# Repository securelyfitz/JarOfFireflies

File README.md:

# Jar of Fireflies
ATtiny-based Jar of Fireflies soldering project with inspiration and reuse from jason webb's https://github.com/jasonwebb/Jar-of-Fireflies

## Hardware Description
This project is intended to be a simple soldering project based on the ATTiny using only a handful of through-hole components. It uses 3 I/O pins to drive 6 charlieplexed LEDs, and an additional 2 I/O pins to control a capacitive sensor.

I originally intended to have the jar's metal ring be touch sensitive alone. However, for cap sensing to work, you need to be grounded, and a PCB inside a glass jar isn't exactly grounded. To account for that, there are several exposed ground pads just inside the ring - touch the ring and one of those pads, and the cap sensing should work.

## Bill of Materials:
* 3x 150 Ohm Resistor
* 2x 1K Ohm Resistor
* 1x 1M Ohm Resistor
* 1x ATTiny85 8-DIP
* 1x 20mm CR2032 holder and battery
* (optional) 1x SMT SPST-NO reset button

##Building
See the PDF for step by step images of building the pcb.

All of the components are labeled right on the board. Rev 1.0 of the board had a minor issue where R4 and R5 were swapped, if you have a Rev 1.0 board, it probably has a sticker correcting it.

You can optionally put the battery holder on the bottom of the board, to keep it out of reach of small hands. Just be sure to trim the pointy leads after soldering.

I used 30 gague wire and gullwing reverse-mount LEDs I had lying around. I soldered 2 LEDs in opposite polarity along each pair of wires. This mean I don't have to worry about the polarity when i solder it to the PCB. I did leave 6 pads for LEDs in case you want to do it the normal way.

##Software Description
This code is an Arduino sketch. I used the Sparkfun TinyAVR Programmer and follow the linked hookup guide to get it working: https://www.sparkfun.com/products/11801

The code for lighting the Charlieplexed LED's is cut and pasted from Jason Webb's project linked above. The code for sensing the capacitive buttons is based on Paul Stoffregen's updated CapacitiveSensor libarry: https://github.com/PaulStoffregen/CapacitiveSensor 

I rely heavily on global variables, and use the state and values to determine what to display on any given iteration. This allows me to responsively check the capsense button without dealing with interrupts.

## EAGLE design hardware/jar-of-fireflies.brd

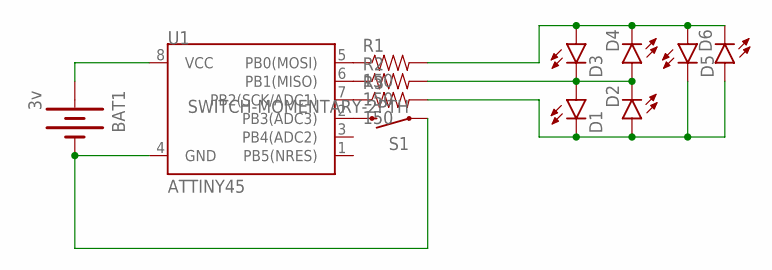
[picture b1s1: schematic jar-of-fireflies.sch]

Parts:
BAT1: 3v; BATTCOM_20MM_PTH
D1, D2, D3, D4, D5, D6: LED3MM
R1, R2, R3: 150; AXIAL-0.4
S1: SWITCH-MOMENTARY-2PTH; TACTILE-PTH
U1: ATTINY45; DIP08

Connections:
GND: BAT1.2 (-), S1.1, U1.4 (GND)
unnamed: R1.P$1 (1), U1.5 (PB0(MOSI))
unnamed: R2.P$1 (1), U1.6 (PB1(MISO))
unnamed: R3.P$1 (1), U1.7 (PB2(SCK/ADC1))
unnamed: S1.3 (2), U1.2 (PB3(ADC3))
unnamed: D3.A, D4.K (C), D5.A, D6.K (C), R1.P$2 (2)
unnamed: D1.K (C), D2.A, D5.K (C), D6.A, R3.P$2 (2)
unnamed: D1.A, D2.K (C), D3.K (C), D4.A, R2.P$2 (2)
VCC: BAT1.1 (+), U1.8 (VCC)

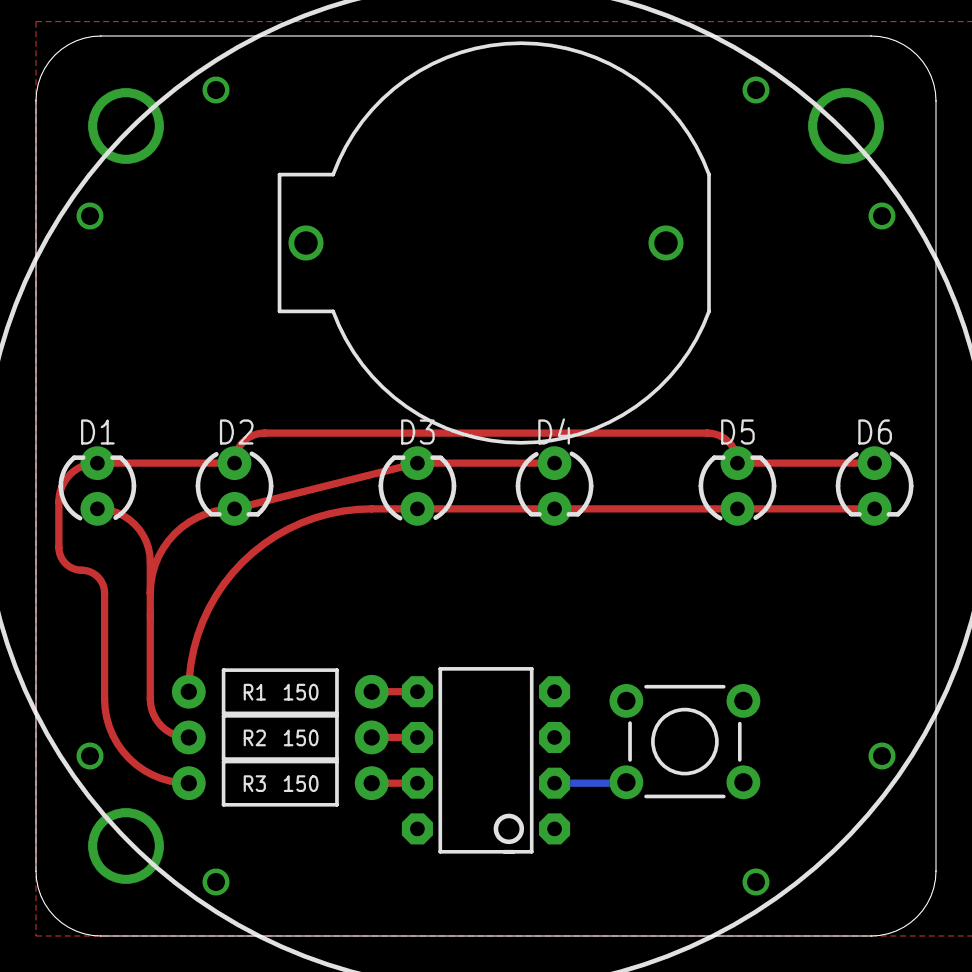
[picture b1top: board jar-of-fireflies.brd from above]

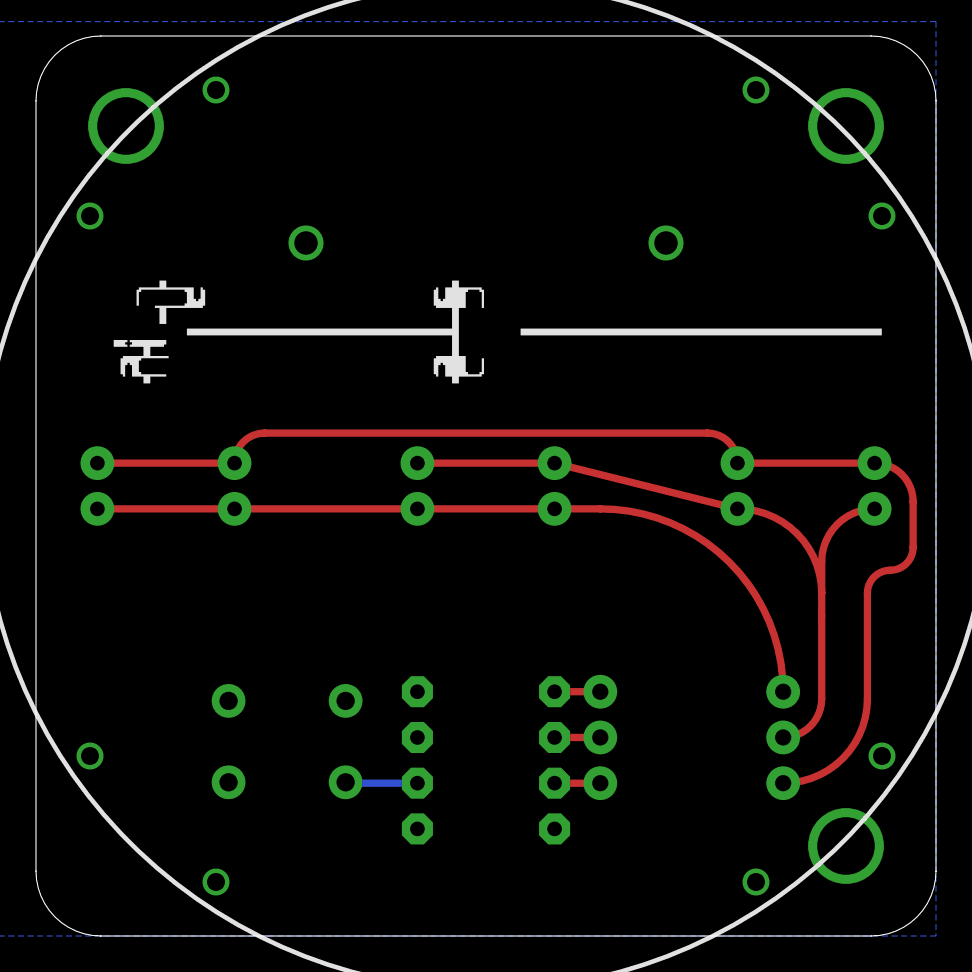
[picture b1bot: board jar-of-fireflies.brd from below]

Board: 2 copper layers, 50.0 x 50.0 mm, 18 parts (3 on the bottom side), 9 nets.

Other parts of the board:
U$1: SECURINGHARDWAREDOTCOM
U$2, U$3, U$4, U$5, U$6: FIREFLY

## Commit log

2016-05-31 first revision of a attiny-based jar of fireflies board that fits in a narrow-mouth mason jar lid.
2016-05-31 Rev 1.1: fixed swapped 1M and 1K resistors, incremented version number.
2016-06-05 moved hardware files into subdirectory
2016-06-05 adding arduino sketch
2016-06-05 adding some notes and instructions
2016-06-05 adding PDF with step by step build images (for kids! and cause words are hard.)
2016-06-05 adding some todos to code
2016-07-10 up to rev 1.2. Gave up on touch sense, replaced with through-hole switch, fewer components!
2016-07-10 putting files in the right place

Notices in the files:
parts and their libraries:
SparkFun-Electromechanical: Licensing: Creative Commons ShareAlike 4.0 International - https://creativecommons.org/licenses/by-sa/4.0
